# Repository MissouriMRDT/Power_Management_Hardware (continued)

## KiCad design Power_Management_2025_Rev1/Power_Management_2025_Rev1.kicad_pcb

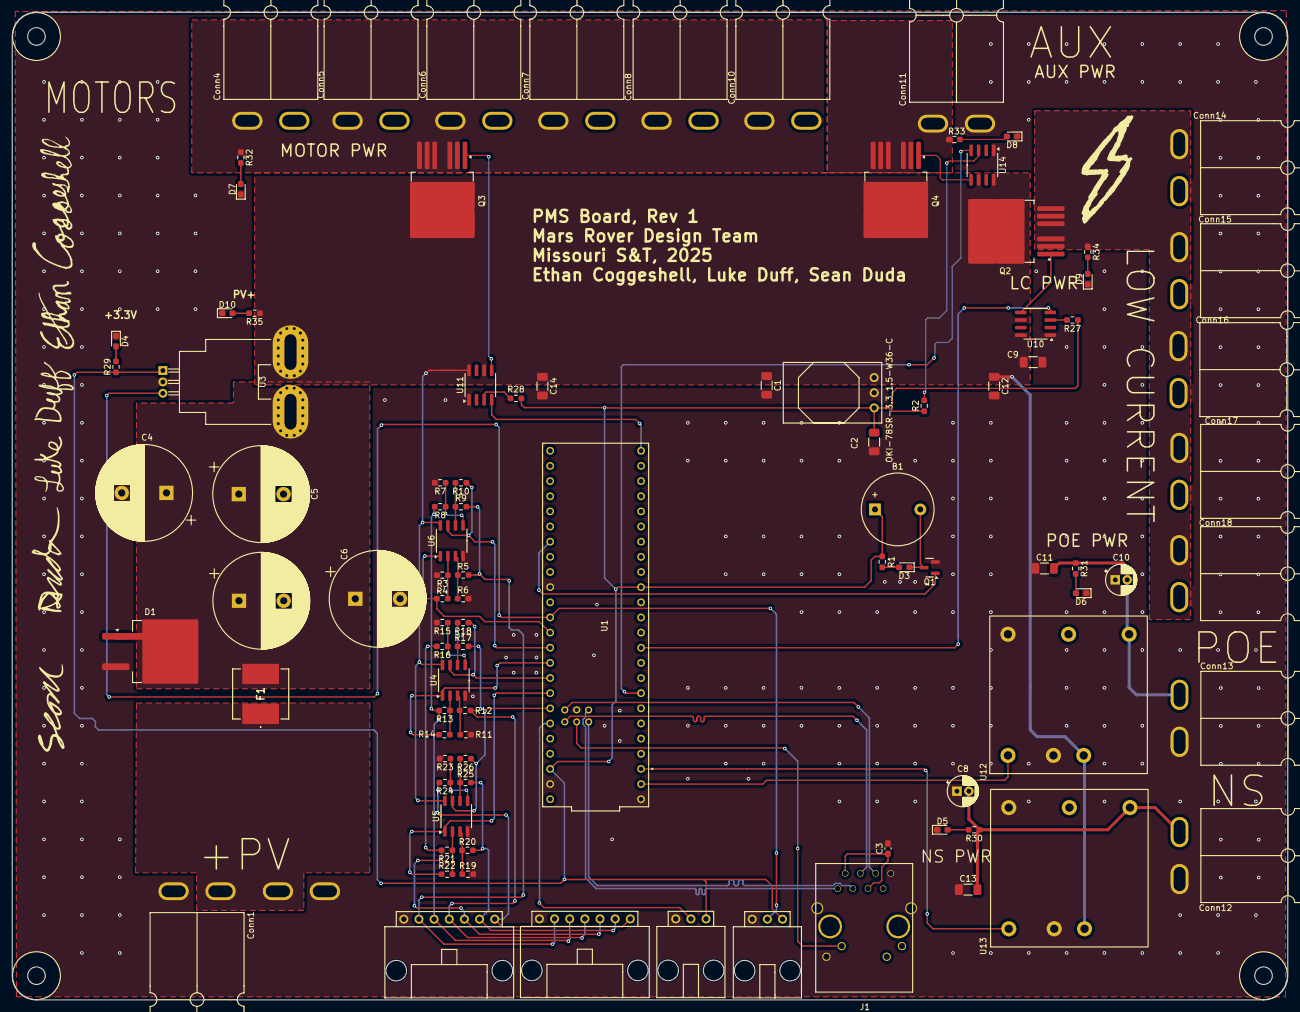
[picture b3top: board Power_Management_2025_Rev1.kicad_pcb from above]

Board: 2 copper layers, 213.9 x 165.6 mm, 100 parts (1 on the bottom side), 63 nets.

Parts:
B1: Buzzer; Buzzer_12x9.5RM7.6
C1, C2, C9, C11, C12, C13, C14: 10uF; C_1206_3216Metric_Pad1.33x1.80mm_HandSolder
C3: 0.1uF; C_0603_1608Metric_Pad1.08x0.95mm_HandSolder
C4, C5, C6, C7: 1000uF; CP_Radial_D16.0mm_P7.50mm
C8, C10: 22uF; CP_Radial_D5.0mm_P2.00mm
Conn1, Conn4, Conn5, Conn6, Conn7, Conn8, Conn10, Conn11, Conn12, Conn13, Conn14, Conn15, Conn16, Conn17, Conn18, Conn19: AndersonPP; Square_Anderson_2_H_Side_By_Side_PV
Conn2, Conn20: Molex_SL_07; MOLEX_SL_07_Horizontal
Conn3, Conn9: Molex_SL_03; MOLEX_SL_03_Horizontal
D1: D_Schottky; TO-263-2_TabPin1
D3: RED; D_0603_1608Metric_Pad1.05x0.95mm_HandSolder
D4, D5, D6, D7, D8, D9, D10: GREEN; D_0603_1608Metric_Pad1.05x0.95mm_HandSolder
F1: Fuse; 3140167
H1, H2, H3, H4: MountingHole; 4_40_Hole_Corner
J1: RJ45_LED_Shielded; RJ45_Teensy
Q1: BSS138; SOT-23
Q2, Q3, Q4: IPB180N10S4-02; TO-263-6
R1, R29: 100; R_0603_1608Metric_Pad0.98x0.95mm_HandSolder
R2, R27, R28: 5.1k; R_0603_1608Metric_Pad0.98x0.95mm_HandSolder
R3, R5, R8, R9, R12, R13, R16, R17, R20, R21, R24, R25: 47k; R_0603_1608Metric_Pad0.98x0.95mm_HandSolder
R4, R6, R7, R10, R11, R14, R15, R18, R19, R22, R23, R26: 39k; R_0603_1608Metric_Pad0.98x0.95mm_HandSolder
R30, R31, R32, R33, R34, R35: 1.5k; R_0603_1608Metric_Pad0.98x0.95mm_HandSolder
U1: Teensy4.1_DEV-16771; Teensy_4_1_Ethernet
U2: OKI-78SR-3.3_1.5-W36-C; OKI_Horizontal
U3: ACS756xCB-050B-PFF; Allegro_CB_PFF
U4, U5, U6: Opamp_Dual; SO-8_3.9x4.9mm_P1.27mm
U10, U11, U14: LT1910; SOIC-8_3.9x4.9mm_P1.27mm
U12, U13: PKE3316ZPI

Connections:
+3.3V: B1.1 (V+), C2.1, Conn3.1, Conn9.1, R1.1, R2.1, R27.1, R28.1, R29.1, U1.3.3V_1 (3.3V), U1.3.3V_2 (3.3V), U2.3 (OUT), U3.1 (VCC)
AUX_EN: U1.6 (OUT1D), U14.4 (IN)
AUX_PWR: Conn11.4 (PV+), Q4.2 (S), Q4.3 (S), Q4.5 (S), Q4.6 (S), Q4.7 (S), R33.1
BUZZER: Q1.1 (G), U1.39 (A15)
CELL1: Conn2.6, Conn20.6, R5.2, R9.2
CELL2: Conn2.5, Conn20.5, R8.2, R13.2
CELL3: Conn2.4, Conn20.4, R12.2, R17.2
CELL4: Conn2.3, Conn20.3, R16.2, R21.2
CELL5: Conn2.2, Conn20.2, R20.2, R25.2
CELL6: Conn2.1, Conn20.1, R24.2
CELL_SENSE_1: R4.1, U1.15 (A1), U6.1
CELL_SENSE_2: R10.1, U1.16 (A2), U6.7
CELL_SENSE_3: R14.1, U1.17 (A3), U4.1
CELL_SENSE_4: R18.1, U1.18 (A4), U4.7
CELL_SENSE_5: R22.1, U1.19 (A5), U5.1
CELL_SENSE_6: R26.1, U1.20 (A6), U5.7
CURRENT_SENSE: Conn3.2, U1.14 (A0), U3.3 (VIOUT)
GND: C1.2, C2.2, C3.2, C4.2, C5.2, C6.2, C7.2, C8.1, C9.2, C10.1, C11.1, C12.2, C13.1, C14.2, Conn1.1 (GND), Conn2.7, Conn3.3, Conn4.1 (GND), Conn5.1 (GND), Conn6.1 (GND), Conn7.1 (GND), Conn8.1 (GND), Conn9.3, Conn10.1 (GND), Conn11.1 (GND), Conn12.1 (GND), Conn13.1 (GND), Conn14.1 (GND), Conn15.1 (GND), Conn16.1 (GND), Conn17.1 (GND), Conn18.1 (GND), Conn19.1 (GND), Conn20.7, D1.2 (A), D4.1 (K), D5.1 (K), D6.1 (K), D7.1 (K), D8.1 (K), D9.1 (K), D10.1 (K), J1.8, J1.9, J1.SH, Q1.2 (S), R3.2, R6.2, R7.2, R11.2, R15.2, R19.2, R23.2, U1.GND1 (GND), U1.GND2 (GND), U1.GND3 (GND), U1.GND5 (GND), U2.2 (GND), U3.2 (GND), U4.4 (V-), U5.4 (V-), U6.4 (V-), U10.1 (GND), U11.1 (GND), U12.2 (VIN-), U12.6 (VOUT-), U13.2 (VIN-), U13.6 (VOUT-), U14.1 (GND)
IP-: C1.1, C9.1, C12.1, C14.1, Q2.4 (D), Q3.4 (D), Q4.4 (D), R35.1, U2.1 (IN), U3.5 (IP-), U4.8 (V+), U5.8 (V+), U6.8 (V+), U10.6 (SENSE), U10.8 (V+), U11.6 (SENSE), U11.8 (V+), U12.3 (VIN+), U13.3 (VIN+), U14.6 (SENSE), U14.8 (V+)
LC_EN: U1.9 (OUT1C), U10.4 (IN)
LED: J1.10, U1.LED
LOW_CURRENT_PWR: Conn14.4 (PV+), Conn15.4 (PV+), Conn16.4 (PV+), Conn17.4 (PV+), Conn18.4 (PV+), Q2.2 (S), Q2.3 (S), Q2.5 (S), Q2.6 (S), Q2.7 (S), R34.1
MOTOR_EN: U1.32 (OUT1B), U11.4 (IN)
MOTOR_PWR: Conn4.4 (PV+), Conn5.4 (PV+), Conn6.4 (PV+), Conn7.4 (PV+), Conn8.4 (PV+), Conn10.4 (PV+), Q3.2 (S), Q3.3 (S), Q3.5 (S), Q3.6 (S), Q3.7 (S), R32.1
NS_24V: C8.2, C13.2, Conn12.4 (PV+), R30.1, U13.4 (VOUT+)
NS_ENABLE: U1.1 (TX1), U13.1 (ON/OFF)
unnamed: B1.2 (V-), D3.1 (K), Q1.3 (D)
unnamed: C3.1, J1.2, J1.5
unnamed: D3.2 (A), R1.2
unnamed: D4.2 (A), R29.2
unnamed: D5.2 (A), R30.2
unnamed: D6.2 (A), R31.2
unnamed: D7.2 (A), R32.2
unnamed: D8.2 (A), R33.2
unnamed: D9.2 (A), R34.2
unnamed: D10.2 (A), R35.2
unnamed: Q2.1 (G), U10.5 (GATE)
unnamed: Q3.1 (G), U11.5 (GATE)
unnamed: Q4.1 (G), U14.5 (GATE)
unnamed: R11.1, R12.1, U4.3 (+)
unnamed: R13.1, R14.2, U4.2 (-)
unnamed: R15.1, R16.1, U4.5 (+)
unnamed: R17.1, R18.2, U4.6 (-)
unnamed: R19.1, R20.1, U5.3 (+)
unnamed: R21.1, R22.2, U5.2 (-)
unnamed: R23.1, R24.1, U5.5 (+)
unnamed: R25.1, R26.2, U5.6 (-)
unnamed: R5.1, R6.1, U6.3 (+)
unnamed: R3.1, R4.2, U6.2 (-)
unnamed: R7.1, R8.1, U6.5 (+)
unnamed: R9.1, R10.2, U6.6 (-)
unnamed: R27.2, U10.3 (FAULT)
unnamed: R28.2, U11.3 (FAULT)
unnamed: R2.2, U14.3 (FAULT)
POE_24V: C10.2, C11.2, Conn13.4 (PV+), R31.1, U12.4 (VOUT+)
POE_ENABLE: U1.0 (RX1), U12.1 (ON/OFF)
PV+: Conn1.4 (PV+), Conn19.4 (PV+), F1.1
PV-: C4.1, C5.1, C6.1, C7.1, D1.1 (K), F1.2, U3.4 (IP+)
RX+: J1.4, U1.R+
RX-: J1.6, U1.R-
TEMP_SENSE: Conn9.2, U1.21 (A7)
TX+: J1.1, U1.TX+
TX-: J1.3, U1.TX-

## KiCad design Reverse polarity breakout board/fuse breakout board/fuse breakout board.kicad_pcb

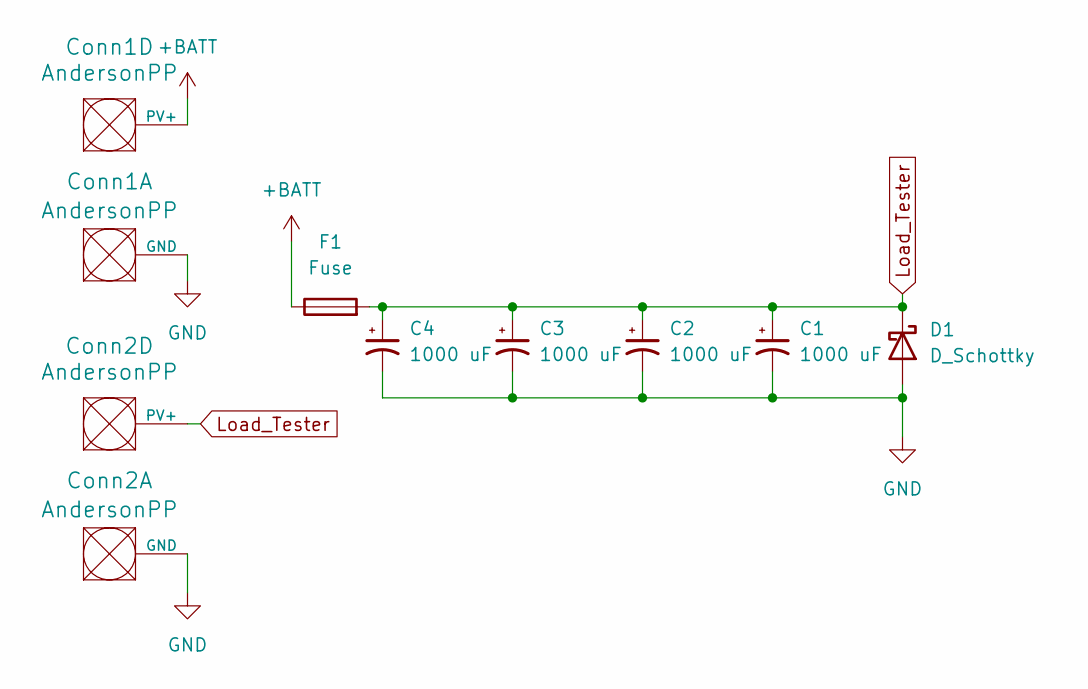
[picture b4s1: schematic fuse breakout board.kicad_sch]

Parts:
C1, C2, C3, C4: 1000 uF; CP_Radial_D16.0mm_P7.50mm
Conn1, Conn2: AndersonPP; Square_Anderson_2_H_Side_By_Side_PV
D1: D_Schottky; TO-263-2_TabPin1
F1: Fuse; 3140167

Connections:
+BATT: Conn1.4 (PV+), F1.1
GND: C1.2, C2.2, C3.2, C4.2, Conn1.1 (GND), Conn2.1 (GND), D1.2 (A)
Load_Tester: C1.1, C2.1, C3.1, C4.1, Conn2.4 (PV+), D1.1 (K), F1.2

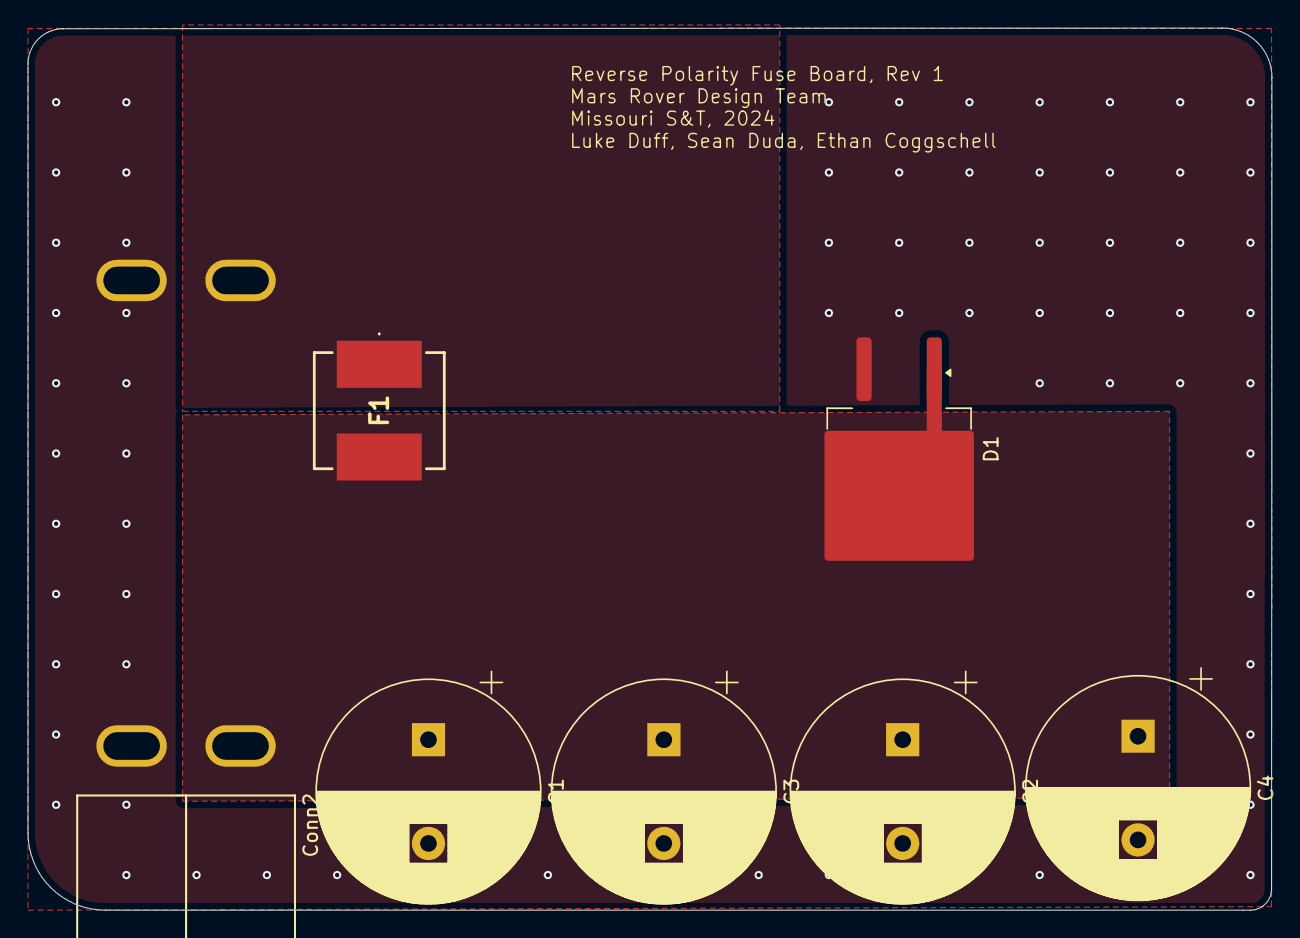
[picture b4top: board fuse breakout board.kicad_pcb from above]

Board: 2 copper layers, 89.9 x 63.8 mm, 8 parts (1 on the bottom side), 3 nets.

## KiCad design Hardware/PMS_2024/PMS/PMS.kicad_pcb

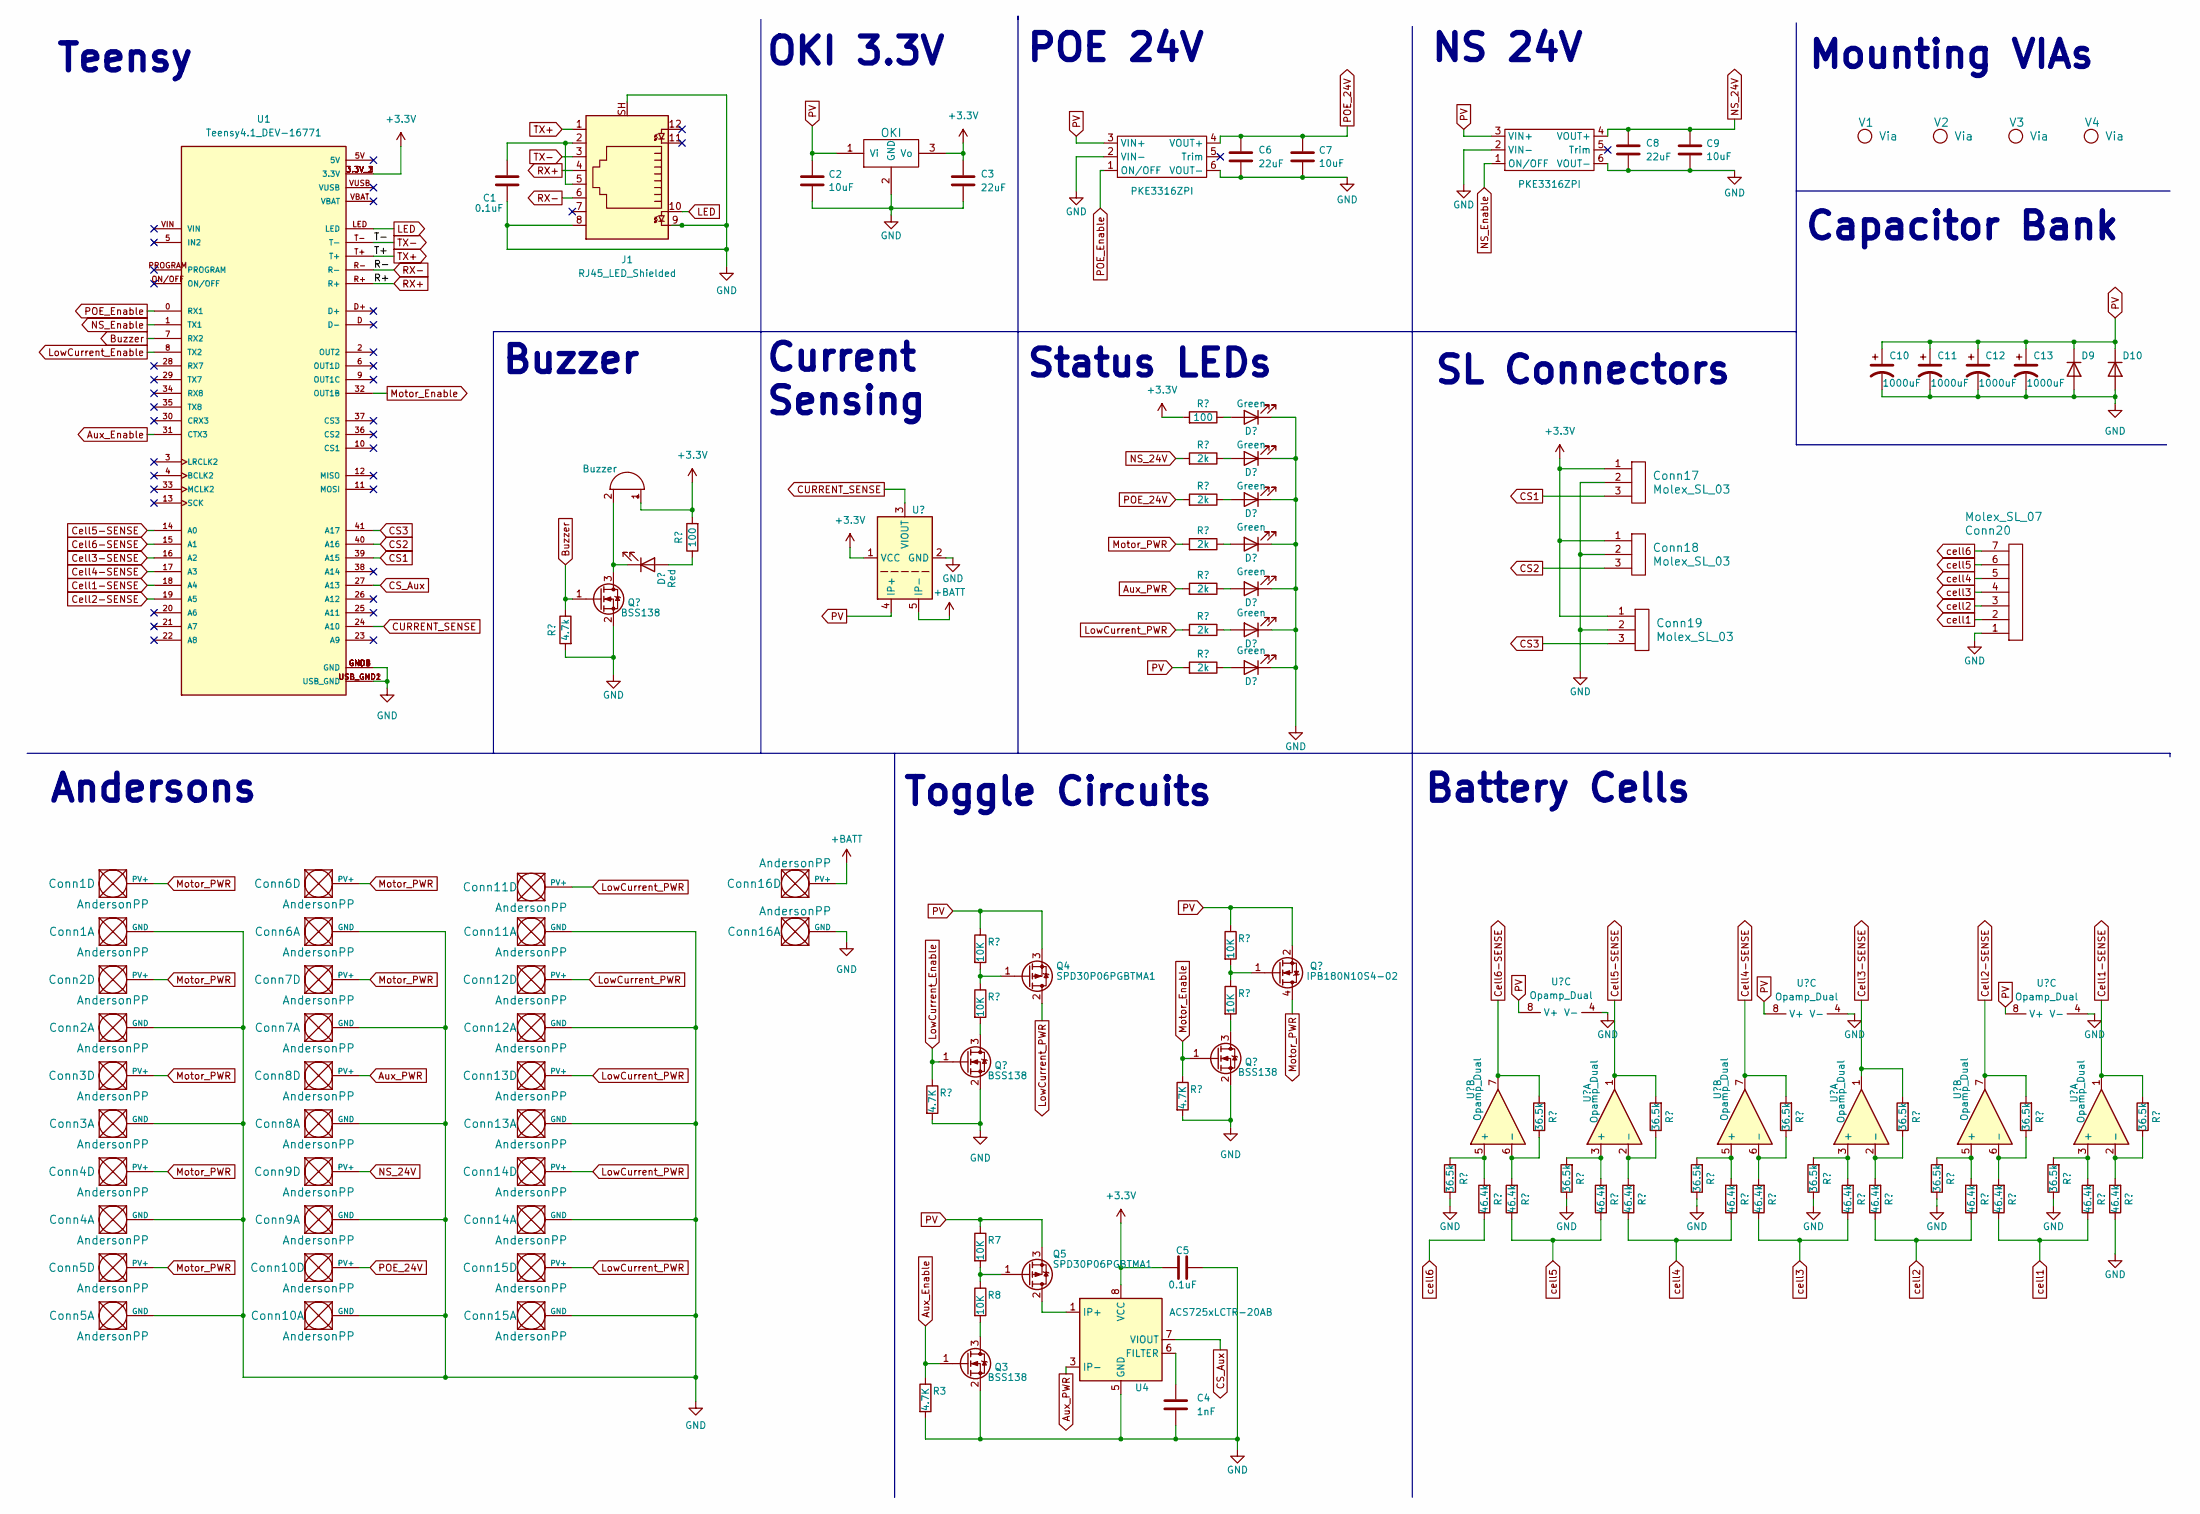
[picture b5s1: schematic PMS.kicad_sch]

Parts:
BZ1: Buzzer; Buzzer_12x9.5RM7.6
C1, C5: 0.1uF; C_0603_1608Metric_Pad1.08x0.95mm_HandSolder
C2, C7, C9: 10uF; C_1206_3216Metric_Pad1.33x1.80mm_HandSolder
C3: 22uF; C_0603_1608Metric_Pad1.08x0.95mm_HandSolder
C4: 1nF; C_0603_1608Metric_Pad1.08x0.95mm_HandSolder
C6, C8: 22uF; CP_Radial_D5.0mm_P2.00mm
C10, C11, C12, C13: 1000uF; CP_Radial_D16.0mm_P7.50mm
Conn1, Conn2, Conn3, Conn4, Conn5, Conn6, Conn7, Conn8, Conn9, Conn10, Conn11, Conn12, Conn13, Conn14, Conn15: AndersonPP; Square_Anderson_2_H_Stacked
Conn16: AndersonPP; Square_Anderson_2_H_Side_By_Side_PV
Conn17, Conn18, Conn19: Molex_SL_03; MOLEX_SL_03_Horizontal
Conn20: Molex_SL_07; MOLEX_SL_07_Horizontal
D1: Red; LED_0603_1608Metric_Pad1.05x0.95mm_HandSolder
D2, D3, D4, D5, D6, D7, D8: Green; LED_0603_1608Metric_Pad1.05x0.95mm_HandSolder
D9, D10: 1.5KE36A+; D_DO-201_P5.08mm_Vertical_KathodeUp
J1: RJ45_LED_Shielded; RJ45_Teensy
Q1, Q2, Q3, Q6: BSS138; SOT-23
Q4, Q5: SPD30P06PGBTMA1; TO-252-2
Q7: IPB180N10S4-02; TO-263-6
R1: 4.7k; R_0603_1608Metric_Pad0.98x0.95mm_HandSolder
R2, R10: 100; R_0603_1608Metric_Pad0.98x0.95mm_HandSolder
R3, R4, R9: 4.7K; R_0603_1608Metric_Pad0.98x0.95mm_HandSolder
R5, R6, R7, R8, R17, R18: 10K; R_0603_1608Metric_Pad0.98x0.95mm_HandSolder
R11, R12, R13, R14, R15, R16: 2k; R_0603_1608Metric_Pad0.98x0.95mm_HandSolder
R19, R22, R23, R26, R27, R30, R31, R34, R35, R38, R39, R42: 36.5k; R_0603_1608Metric_Pad0.98x0.95mm_HandSolder
R20, R21, R24, R25, R28, R29, R32, R33, R36, R37, R40, R41: 46.4k; R_0603_1608Metric_Pad0.98x0.95mm_HandSolder
U1: Teensy4.1_DEV-16771; Teensy_4_1_Ethernet; PARTREV 4.1
U2: OKI; OKI_Horizontal
U3: ACS758xCB-200B-PFF; Allegro_CB_PFF
U4: ACS725xLCTR-20AB; SOIC-8_3.9x4.9mm_P1.27mm
U5, U7: PKE3316ZPI
U6, U8, U9: Opamp_Dual; SO-8_3.9x4.9mm_P1.27mm
V1, V2, V3, V4: Via; 4_40_Hole

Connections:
+3.3V: BZ1.1 (-), C3.1, C5.1, Conn17.1, Conn18.1, Conn19.1, R2.2, R10.2, U1.3.3V_1 (3.3V), U1.3.3V_2 (3.3V), U1.3.3V_3 (3.3V), U2.3 (Vo), U3.1 (VCC), U4.8 (VCC)
+BATT: Conn16.4 (PV+), U3.5 (IP-)
Aux_Enable: Q3.1 (G), R3.1, U1.31 (CTX3)
Aux_PWR: Conn8.4 (PV+), R14.2, U4.3 (IP-), U4.4 (IP-)
Buzzer: Q1.1 (G), R1.1, U1.7 (RX2)
CS1: Conn17.3, U1.39 (A15)
CS2: Conn18.3, U1.40 (A16)
CS3: Conn19.3, U1.41 (A17)
CS_Aux: U1.27 (A13), U4.7 (VIOUT)
CURRENT_SENSE: U1.24 (A10), U3.3 (VIOUT)
Cell1-SENSE: R42.2, U1.18 (A4), U9.1
Cell2-SENSE: R38.2, U1.19 (A5), U9.7
Cell3-SENSE: R34.2, U1.16 (A2), U8.1
Cell4-SENSE: R30.2, U1.17 (A3), U8.7
Cell5-SENSE: R26.2, U1.14 (A0), U6.1
Cell6-SENSE: R22.2, U1.15 (A1), U6.7
GND: C1.1, C2.2, C3.2, C4.1, C5.2, C6.2, C7.2, C8.2, C9.2, C10.2, C11.2, C12.2, C13.2, Conn1.1 (GND), Conn2.1 (GND), Conn3.1 (GND), Conn4.1 (GND), Conn5.1 (GND), Conn6.1 (GND), Conn7.1 (GND), Conn8.1 (GND), Conn9.1 (GND), Conn10.1 (GND), Conn11.1 (GND), Conn12.1 (GND), Conn13.1 (GND), Conn14.1 (GND), Conn15.1 (GND), Conn16.1 (GND), Conn17.2, Conn18.2, Conn19.2, Conn20.1, D2.1 (K), D3.1 (K), D4.1 (K), D5.1 (K), D6.1 (K), D7.1 (K), D8.1 (K), D9.2 (A), D10.2 (A), J1.8, J1.9, J1.SH, Q1.2 (S), Q2.2 (S), Q3.2 (S), Q6.2 (S), R1.2, R3.2, R4.2, R9.2, R19.1, R23.1, R27.1, R31.1, R35.1, R39.1, R41.1, U1.GND1 (GND), U1.GND2 (GND), U1.GND3 (GND), U1.GND4 (GND), U1.GND5 (GND), U1.USB_GND1 (USB_GND), U1.USB_GND2 (USB_GND), U2.2 (GND), U3.2 (GND), U4.5 (GND), U5.2 (VIN-), U5.6 (VOUT-), U6.4 (V-), U7.2 (VIN-), U7.6 (VOUT-), U8.4 (V-), U9.4 (V-)
LED: J1.10, U1.LED
LowCurrent_Enable: Q2.1 (G), R4.1, U1.8 (TX2)
LowCurrent_PWR: Conn11.4 (PV+), Conn12.4 (PV+), Conn13.4 (PV+), Conn14.4 (PV+), Conn15.4 (PV+), Q4.2 (D), R15.2
Motor_Enable: Q6.1 (G), R9.1, U1.32 (OUT1B)
Motor_PWR: Conn1.4 (PV+), Conn2.4 (PV+), Conn3.4 (PV+), Conn4.4 (PV+), Conn5.4 (PV+), Conn6.4 (PV+), Conn7.4 (PV+), Q7.4 (D), R13.2
NS_24V: C8.1, C9.1, Conn9.4 (PV+), R11.2, U7.4 (VOUT+)
NS_Enable: U1.1 (TX1), U7.1 (ON/OFF)
unnamed: BZ1.2 (+), D1.1 (K), Q1.3 (D)
unnamed: C1.2, J1.2, J1.5
unnamed: D1.2 (A), R2.1
unnamed: D2.2 (A), R10.1
unnamed: D3.2 (A), R11.1
unnamed: D4.2 (A), R12.1
unnamed: D5.2 (A), R13.1
unnamed: D6.2 (A), R14.1
unnamed: D7.2 (A), R15.1
unnamed: D8.2 (A), R16.1
unnamed: Q2.3 (D), R6.2
unnamed: Q3.3 (D), R8.2
unnamed: Q4.1 (G), R5.2, R6.1
unnamed: Q5.2 (D), U4.1 (IP+), U4.2 (IP+)
unnamed: Q5.1 (G), R7.2, R8.1
unnamed: Q6.3 (D), R18.2
unnamed: Q7.1 (G), R17.2, R18.1
unnamed: C4.2, U4.6 (FILTER)
unnamed: R23.2, R24.2, U6.3 (+)
unnamed: R25.2, R26.1, U6.2 (-)
unnamed: R19.2, R20.2, U6.5 (+)
unnamed: R21.2, R22.1, U6.6 (-)
unnamed: R31.2, R32.2, U8.3 (+)
unnamed: R33.2, R34.1, U8.2 (-)
unnamed: R27.2, R28.2, U8.5 (+)
unnamed: R29.2, R30.1, U8.6 (-)
unnamed: R39.2, R40.2, U9.3 (+)
unnamed: R41.2, R42.1, U9.2 (-)
unnamed: R35.2, R36.2, U9.5 (+)
unnamed: R37.2, R38.1, U9.6 (-)
POE_24V: C6.1, C7.1, Conn10.4 (PV+), R12.2, U5.4 (VOUT+)
POE_Enable: U1.0 (RX1), U5.1 (ON/OFF)
PV: C2.1, C10.1, C11.1, C12.1, C13.1, D9.1 (K), D10.1 (K), Q4.3 (S), Q5.3 (S), Q7.2 (S), Q7.3 (S), Q7.5 (S), Q7.6 (S), Q7.7 (S), R5.1, R7.1, R16.2, R17.1, U2.1 (Vi), U3.4 (IP+), U5.3 (VIN+), U6.8 (V+), U7.3 (VIN+), U8.8 (V+), U9.8 (V+)
RX+: J1.4, U1.R+
RX-: J1.6, U1.R-
TX+: J1.1, U1.T+
TX-: J1.3, U1.T-
cell1: Conn20.2, R37.1, R40.1
cell2: Conn20.3, R33.1, R36.1
cell3: Conn20.4, R29.1, R32.1
cell4: Conn20.5, R25.1, R28.1
cell5: Conn20.6, R21.1, R24.1
cell6: Conn20.7, R20.1

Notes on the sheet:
Teensy
OKI 3.3V
NS 24V
SL Connectors
Mounting VIAs
Toggle Circuits
Current Sensing
Buzzer
Andersons
Status LEDs
Capacitor Bank
Battery Cells
POE 24V

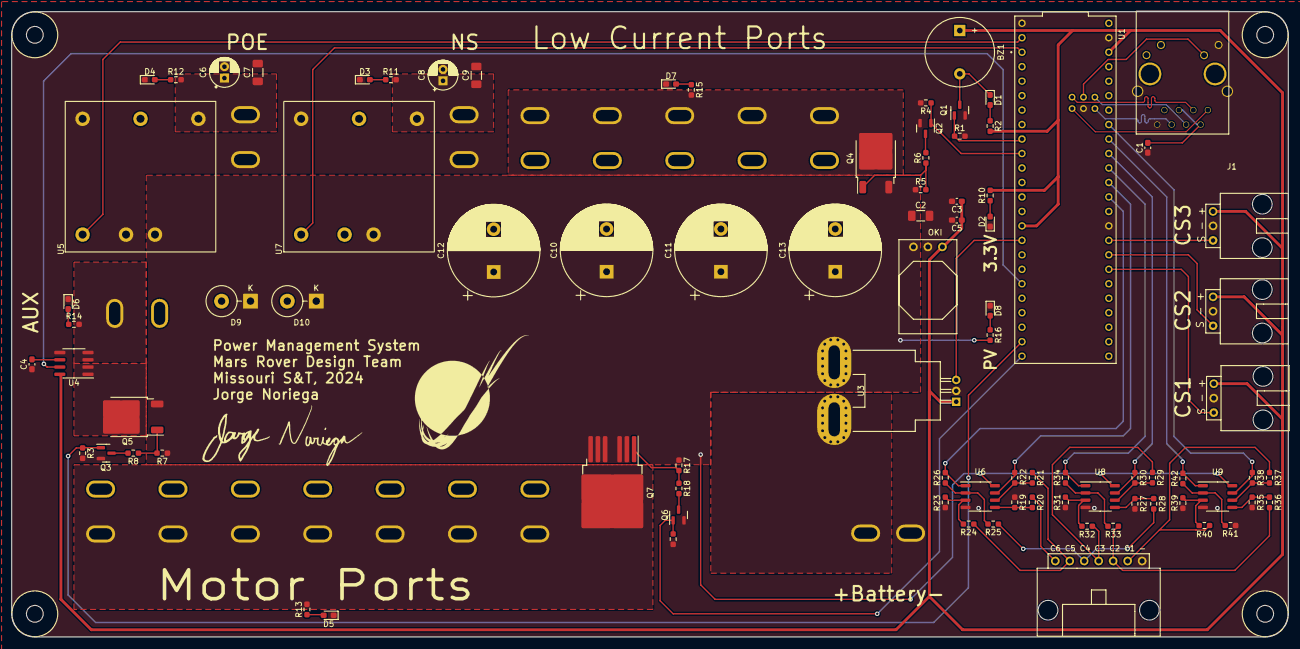
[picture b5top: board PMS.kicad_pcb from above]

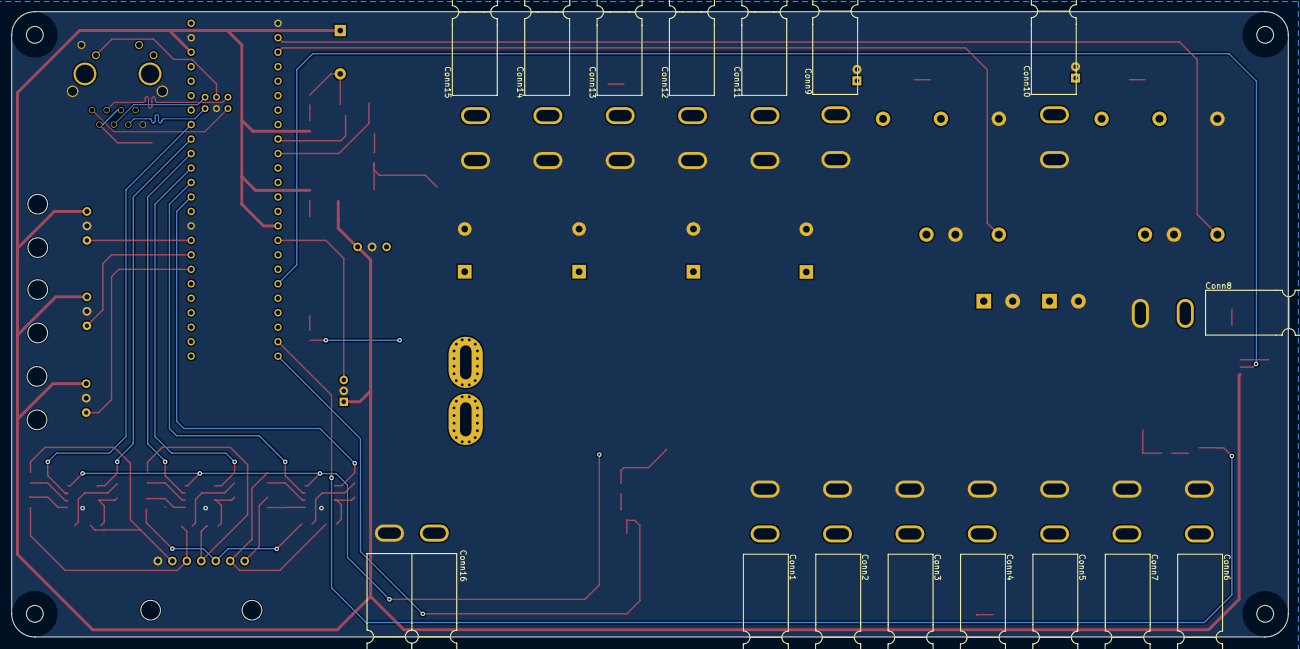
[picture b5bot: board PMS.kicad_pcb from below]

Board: 2 copper layers, 224.0 x 109.7 mm, 107 parts (16 on the bottom side), 67 nets.

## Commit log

2024-03-01 Started PMS
    Started Schematic
2024-03-05 Layout Started
2024-03-07 Finished General Layout
    All trace work still needs to be done
    General layout is finished
2024-03-13 Changed Layout
    Changed the entire layout
    Most traces still need to be routed
2024-03-14 Finished Layout + Traces
    Finished Layout
    Silkscreens still need to be added
2024-03-18 Added Silkscreens
    Added Signature and Silkscreens
2024-03-20 Layout Changes
    Added SL labels
    Moved some traces, away from planes
2024-03-21 Resistor Changes
    Added a PV LED
    Changed some resistor values
2024-03-21 Trace change
    Moved trace for a wider GND plane
2024-03-24 Footprint Change
2024-03-27 created gerbs
2024-04-03 Created step file
2024-04-13 Fixed ground plane to caps
2024-04-13 Revert "Fixed ground plane to caps"
    This reverts commit 0f93090606acd132730fc91c24dbd6cd32ab7d8f.
2024-09-26 Started PMS
    Andersons, 3.3V oki and 5V oki, put in teensie, added some inputs and outputs, cell sensing wires.
2024-09-28 worked on PDR schmadic
    Worked on current sensors and buzzer and put together RJ-45
2024-10-01 I worked on Anderson and stuff
2024-10-01 trying something new
2024-10-01 Added components
    Added cell sensing opamps, LC and motor gate drivers, external current sense.
2024-10-01 Made Fun 2 trying transfer
2024-10-01 Transfered Fun2 to PMS 2025
    It worked if you make a new project you can copy and paste into other projects
2024-10-01 Pausing work for a bit
2024-10-01 More formating done
2024-10-01 more format
2024-10-03 Added few components and cleaned up schematic
    Added few more andersons and cleaned up schematic
2024-10-03 Added components and cleaned up schematic
2024-10-05 Corrected POE and NS converter
    and added signal labels
2024-10-09 Added set of andersons
2024-10-09 Cleaned up schematic
2024-10-16 Made Changes from word doc
    flipped power flags on current sensing, switched all PV pins to +BATT, added labels to LEDs, removed pull down resistor from buzzer circuit and flipped polarity of buzzer, Changed LED resistors to 1.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
2024-10-17 Finished changes
    removed additional andersons, capitalized all labels, added another gat driver circuit (unfinished)
2024-10-19 Added aux gate driver
    rearranged some of the circuits to make room for AUX gate driver
2024-10-22 Finished reverse voltage protection circuit
    The reverse voltage protection circuit was finished with a shottky diode, and a PTC fuse. Then an additional set of current sensing wires and battery voltage andersons were also placed for smart batt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
2024-10-24 Footprint assignments
2024-10-24 Revers polarity breakout
    yes
2024-10-27 We are almost finished
2024-10-27 Reworked power planes and adjusted cap bank
    Reworked power plane and adjusted cap bank. Created a 35 mill trace from heatsink die to pad off power plane to account for ground connection
2024-10-28 Started on PCB editor
    Started layout grouped components began trace work
2024-10-28 Tracing
    made a few more traces with the buzzer and cap bank
2024-10-29 Added Load Tester andersons and via stitching
    Added load tester andersons and vias to stitch ground planes on the front and back together to prevent capacitance build up and allow current to flow
2024-10-29 Adjusted components for power planes
    Adjusted components for power planes and had the layout reviewed by E-Leads. Changes to follow
2024-10-29 Test
    Test
2024-10-29 Signal LEDs and Mosfets
    Moved the signal LEDs and Mosfets
2024-10-30 More tracework
    Made corrections to schematic and did more tracework on PCB
2024-10-30 Pushing opamp new numbers
2024-10-31 Rearranged component
    We Made power planes
2024-10-31 Finished Rev 1 Design for CDR
    Organized components, laid power planes, ran traces, and finished board edge cuts
2024-10-31 Schematic save
    Schematic save
2024-11-01 Generated Gerbs
2024-11-01 Saved gerbs
2024-11-04 Worked on corrections
    Retraced opamp circuit, fixed diff pair, moved capacitors to be closer to what they filter, increased size of silkscreens, fixed inputs and outputs in relation to opamps and teensie
2024-11-04 Changed Silkscreen
2024-11-05 We changed the planes
2024-11-06 retraced opamp circuit to be more symetric
2024-11-06 corrected a trace
2024-11-06 no changes
2024-11-06 Power plane, diff pair, and mil width fix`
    Fixed Motor power plane, readjusted diff pair, and fixed mil width
2024-11-07 Fixed diff pair and rearranged Cap bank
2024-11-11 Retraced current sense trace, connected opamps to IP-, and made sure no traces in between resistor pads
2024-11-11 Rerouted problematic traces, made low current power plane, added vias in open areas, added signature
2024-11-12 Few board rev changes
2024-11-13 Made some changes that were mentioned at board review. +3.3V still needs to be traced
2024-11-14 Board review changes
2024-11-14 Fixed edge cuts, planes
    Made new edgecuts that made the board whole measurement, We edited the PV+ plane to allow space for signal trace, Move silkscreeen pieces
2024-11-14 Layout complete
    fixed silkscreens, fixed andersons, added memes, rearranged caps.
2024-11-14 Final changes
    Cleaned up 3.3V, moved caps a little, moved SL traces up so they are not near hole
2024-11-14 Fixed 3.3V trace by the op-amps
    Reran the 3.3V trace by the op-amps to go under the teensy instead
2024-11-15 Retraced +3.3V
2024-11-15 Created and verified gerbs file
2024-11-20 Changed caps on LT1910
2025-04-21 Added .gitignore and deleted backups
2025-09-06 Initial setup
2025-09-12 Added workflow
2025-10-01 Added Hierarchys
    Voltage sensing sheet
    Reverse Current Protection Sheet
2025-10-04 Schematics without values
    Votlage Sensing circuit schematic
    Oring controller circuit schematic
    No values for components yet
2025-10-04 Resistor Values
    Added resistor values for everything on voltage sensing circuit
2025-10-05 Added Zener DIodes
2025-10-06 add switching circuit
2025-10-07 fix switch page not showing up
2025-10-07 Changed Flags
2025-10-08 Added pack current sensor
2025-10-10 Current Sensor in Current Protection
    amogus
2025-10-10 switch the LTC7001 gate driver with the LT1910
2025-10-10 make big current sensor go bye bye
2025-10-10 added buzzer circuit
2025-10-10 create 5 switching circuits
2025-10-10 add labels to switching circuits
2025-10-10 Add MCU[WIP] and Ethernet
2025-10-10 added current sense flags to teensy
2025-10-10 Added MCU Flags
2025-10-10 added wiring and Voltage Sense Fix
2025-10-10 added port in voltage sensing
2025-10-10 add POE
2025-10-10 add mosfett and teensy switch pins
2025-10-10 add 2 new POE and replace mosfets
2025-10-12 Current Sensors FABRICATED
    Current Sensor Hierarchy sheet created
    Contains:
    - Network Switch current sensing
    - POE current sensing
    - Low Current current sensing
2025-10-12 BattCSense added
2025-10-14 add new poe page
2025-10-15 add anderson page
2025-10-15 clean up current sensinator
2025-10-15 Replaced Current sensors and made aux current sensor
2025-10-15 Revert "Replaced Current sensors and made aux current sensor"
    This reverts commit 6ac851d0f9d66083f206abad37eab70415909eb9.
2025-10-15 sync previous 2 commits changes correctly
2025-10-15 Added LCD
2025-10-15 Deletes Redundant Flag
2025-10-15 Created Current Sensors in Sensinator
    -Create current sensors for m2, m5, m9, Low Current, Network, and AUX
2025-10-15 Connect Current Sensing Pins
    -Connected pins from Switching Circuits, POE, Andersons, Teensy, and Current-Sensinator
    -A little organization courtesy of Emilio Baeza
2025-10-15 corret poe pins
2025-10-15 kitty!
    5V and 3.3V
2025-10-15 Voltage Dividers on Current Sensors
2025-10-16 include andersons for all LC and teensy enables for m2, m5, and m9
2025-10-22 added power leds
2025-10-23 added fixes for schematic
    redid op amp symbols
    put Xs on teensy
    Put andersons on current protection page
    changed resistor value for buzzer
2025-10-24 add backup anderson on POE
2025-10-24 removed non-existent pin on switchting circuits
2025-10-24 fixed wiring
2025-10-24 Capacitor Change
2025-10-24 added most datasheets [Except Buzzer]
2025-10-25 More footprints added
2025-10-25 added datasheet links
2025-10-25 Buzzer Footprint added
2025-10-25 Changed footprints to handsolder version
2025-10-30 Added mounting holes
    added mounting holes and assigned them a footprint
2025-10-30 anderson footprints
2025-10-30 LCD footprint upload
2025-10-30 Assigned Current Sensor Footprints
2025-10-30 LED Fix
2025-10-30 NOW CURRENT SENSOR FOOTPRINT ASSIGNED!
2025-10-30 reorganize lib folder feet
2025-10-30 move footprints into power managment folder
2025-10-30 Finally assigned the footprints for current sensor, led, poe
2025-10-30 fixed op amp footprint
2025-10-30 Final footprints added
2025-10-30 new connectors
2025-10-30 Teensy connected pcb
2025-10-30 PCB start
2025-10-31 designated an area for each circuit on pcb
2025-11-01 Configuration of parts
2025-11-01 Rearrangement #2
2025-11-01 Deleted Capacitors
2025-11-01 Board before M5 Kill
2025-11-02 Planned layout - before wiring.
2025-11-02 added edge cuts
2025-11-05 Most Traces done
2025-11-05 add more traces
    seems to be just 24V connections left
2025-11-06 Changes before layout review
2025-11-06 experimented with layout
2025-11-06 move ground ring terminal
2025-11-07 Some organization
    + failed artwork footprints added
2025-11-09 layout changes for 24 volt plane
2025-11-09 24 volt plane addition
2025-11-12 do basically everything
    12 hours of our life
2025-11-12 13 hours no silk screen
2025-11-12 17 hours of our lives
2025-11-12 18 Hours and counting...
    -Moved LEDs,
    -Added innocent kitties
2025-11-12 Added Ore to Breakout Board
2025-11-12 Added Adam
2025-11-12 give the board a quick line up
    mosfets and drivers in the center are actually aligned well
2025-11-12 Center schematics and layout for prettiness
2025-11-12 Correct Teensy 3D Model File Name
2025-11-12 add molex models
2025-11-12 Add Power
2025-11-12 add RJ45 models
2025-11-13 change before CDR
2025-11-14 clean up board a tiny bit
    this took way too long
2025-11-14 add title silkscreen
2025-11-14 add light via stitching
    still need to add more via stitching and more test points
2025-11-14 add label for battery sensing molex connector
2025-11-14 Move MRDT Logo; Update footprints
2025-11-15 Testing points started
2025-11-15 Added test points and labels for op amps
    -Also added a MRDT logo to the breakout board
2025-11-16 organize labels
2025-11-17 Via stitched planes
2025-11-18 Move test points and silkscreens
2025-11-18 Remove brainrot
2025-11-19 Add redstone silkscreen
2025-12-10 Add 3D models for mega fits and LCD
2026-02-20 Updated mosfet in schematic
2026-02-20 Added LEDS to layout
2026-02-24 Fixed resistor footprints
